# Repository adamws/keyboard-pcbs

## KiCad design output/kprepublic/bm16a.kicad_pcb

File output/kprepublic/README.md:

## kprepublic/bm16s

[layout](bm16s-kle.json) - [PCB](bm16s.kicad_pcb)

{:loading="lazy"}

[Open in keyboard-layout-editor](http://www.keyboard-layout-editor.com/##@@=0,0&=0,1&=0,2&=0,3;&@=1,0&=1,1&=1,2&=1,3;&@=2,0&=2,1&=2,2&=2,3;&@=3,0&=3,1&=3,2&=3,3)

{:loading="lazy"}

## kprepublic/bm40hsrgb

[layout](bm40hsrgb-kle.json) - [PCB](bm40hsrgb.kicad_pcb)

{:loading="lazy"}

[Open in keyboard-layout-editor](http://www.keyboard-layout-editor.com/##@@_c=#aaaaaa;&=0,0&_c=#ccccccc;&=0,1&=0,2&=0,3&=0,4&=0,5&=0,6&=0,7&=0,8&=0,9&=0,10&_c=#aaaaaa;&=0,11;&@_c=#777777;&=1,0&_c=#ccccccc;&=1,1&=1,2&=1,3&=1,4&=1,5&=1,6&=1,7&=1,8&=1,9&=1,10&_c=#aaaaaa;&=1,11;&@=2,0&_c=#ccccccc;&=2,1&=2,2&=2,3&=2,4&=2,5&=2,6&=2,7&=2,8&=2,9&=2,10&_c=#777777;&=2,11;&@_c=#aaaaaa;&=3,0&=3,1&=3,2&=3,3&=3,4&_w:2;&=3,5&=3,7&_c=#777777;&=3,8&=3,9&=3,10&=3,11)

{:loading="lazy"}

## kprepublic/bm60poker

[layout](bm60poker-kle.json) - [PCB](bm60poker.kicad_pcb)

{:loading="lazy"}

[Open in keyboard-layout-editor](http://www.keyboard-layout-editor.com/##@@_c=#777777;&=0,0&_c=#cccccc;&=0,1&=0,2&=0,3&=0,4&=0,5&=0,6&=0,7&=0,8&=0,9&=0,10&=0,11&=0,12&_c=#aaaaaa&w:2;&=0,13;&@_w:1.5;&=1,0&_c=#cccccc;&=1,1&=1,2&=1,3&=1,4&=1,5&=1,6&=1,7&=1,8&=1,9&=1,10&=1,11&=1,12&_w:1.5;&=1,13;&@_c=#aaaaaa&w:1.75;&=2,0&_c=#cccccc;&=2,2&=2,3&=2,4&=2,5&=2,6&=2,7&=2,8&=2,9&=2,10&=2,11&=2,12&_c=#777777&w:2.25;&=2,13;&@_c=#aaaaaa&w:2.25;&=3,1&_c=#cccccc;&=3,2&=3,3&=3,4&=3,5&=3,6&=3,7&=3,8&=3,9&=3,10&=3,11&_c=#aaaaaa&w:2.75;&=3,13;&@_w:1.25;&=4,0&_w:1.25;&=4,1&_w:1.25;&=4,2&_c=#cccccc&w:6.25;&=4,6&_c=#aaaaaa&w:1.25;&=4,9&_w:1.25;&=4,10&_w:1.25;&=4,12&_w:1.25;&=4,13)

{:loading="lazy"}

## kprepublic/bm60poker_v2

[layout](bm60poker_v2-kle.json) - [PCB](bm60poker_v2.kicad_pcb)

{:loading="lazy"}

[Open in keyboard-layout-editor](http://www.keyboard-layout-editor.com/##@@_c=#777777;&=0,0&_c=#cccccc;&=0,1&=0,2&=0,3&=0,4&=0,5&=0,6&=0,7&=0,8&=0,9&=0,10&=0,11&=0,12&_c=#aaaaaa&w:2;&=0,13;&@_w:1.5;&=1,0&_c=#cccccc;&=1,1&=1,2&=1,3&=1,4&=1,5&=1,6&=1,7&=1,8&=1,9&=1,10&=1,11&=1,12&_w:1.5;&=1,13;&@_c=#aaaaaa&w:1.75;&=2,0&_c=#cccccc;&=2,1&=2,2&=2,3&=2,4&=2,5&=2,6&=2,7&=2,8&=2,9&=2,10&=2,11&_c=#777777&w:2.25;&=2,13;&@_c=#aaaaaa&w:2.25;&=3,0&_c=#cccccc;&=3,1&=3,2&=3,3&=3,4&=3,5&=3,6&=3,7&=3,8&=3,9&=3,10&_c=#aaaaaa&w:2.75;&=3,13;&@_w:1.25;&=4,0&_w:1.25;&=4,1&_w:1.25;&=4,2&_c=#cccccc&w:6.25;&=4,5&_c=#aaaaaa&w:1.25;&=4,9&_w:1.25;&=4,10&_w:1.25;&=4,11&_w:1.25;&=4,13)

{:loading="lazy"}

## kprepublic/bm60rgb

[layout](bm60rgb-kle.json) - [PCB](bm60rgb.kicad_pcb)

{:loading="lazy"}

[Open in keyboard-layout-editor](http://www.keyboard-layout-editor.com/##@@_c=#777777;&=0,0&_c=#cccccc;&=0,1&=0,2&=0,3&=0,4&=0,5&=0,6&=0,7&=0,8&=0,9&=0,10&=0,11&=0,12&_c=#aaaaaa&w:2;&=0,13;&@_w:1.5;&=1,0&_c=#cccccc;&=1,1&=1,2&=1,3&=1,4&=1,5&=1,6&=1,7&=1,8&=1,9&=1,10&=1,11&=1,12&_w:1.5;&=1,13;&@_c=#aaaaaa&w:1.75;&=2,0&_c=#cccccc;&=2,2&=2,3&=2,4&=2,5&=2,6&=2,7&=2,8&=2,9&=2,10&=2,11&=2,12&_c=#777777&w:2.25;&=2,13;&@_c=#aaaaaa&w:2.25;&=3,1&_c=#cccccc;&=3,2&=3,3&=3,4&=3,5&=3,6&=3,7&=3,8&=3,9&=3,10&_c=#aaaaaa&w:1.75;&=3,11&_c=#777777;&=3,12&_c=#cccccc;&=3,13;&@_c=#aaaaaa&w:1.25;&=4,0&_w:1.25;&=4,1&_w:1.25;&=4,2&_c=#777777&w:6.25;&=4,6&_c=#aaaaaa;&=4,9&=4,10&_c=#777777;&=4,11&=4,12&=4,13)

{:loading="lazy"}

## kprepublic/bm60rgb_v2

[layout](bm60rgb_v2-kle.json) - [PCB](bm60rgb_v2.kicad_pcb)

{:loading="lazy"}

[Open in keyboard-layout-editor](http://www.keyboard-layout-editor.com/##@@_c=#777777;&=0,0&_c=#cccccc;&=0,1&=0,2&=0,3&=0,4&=0,5&=0,6&=0,7&=0,8&=0,9&=0,10&=0,11&=0,12&_c=#aaaaaa&w:2;&=0,13;&@_w:1.5;&=1,0&_c=#cccccc;&=1,1&=1,2&=1,3&=1,4&=1,5&=1,6&=1,7&=1,8&=1,9&=1,10&=1,11&=1,12&_w:1.5;&=1,13;&@_c=#aaaaaa&w:1.75;&=2,0&_c=#cccccc;&=2,2&=2,3&=2,4&=2,5&=2,6&=2,7&=2,8&=2,9&=2,10&=2,11&=2,12&_c=#777777&w:2.25;&=2,13;&@_c=#aaaaaa&w:2.25;&=3,1&_c=#cccccc;&=3,2&=3,3&=3,4&=3,5&=3,6&=3,7&=3,8&=3,9&=3,10&_c=#aaaaaa&w:1.75;&=3,11&_c=#777777;&=3,12&_c=#cccccc;&=3,13;&@_c=#aaaaaa&w:1.25;&=4,0&_w:1.25;&=4,1&_w:1.25;&=4,2&_c=#777777&w:6.25;&=4,6&_c=#aaaaaa;&=4,9&=4,10&_c=#777777;&=4,11&=4,12&=4,13)

{:loading="lazy"}

## kprepublic/bm60v2_ec

[layout](bm60v2_ec-kle.json) - [PCB](bm60v2_ec.kicad_pcb)

{:loading="lazy"}

[Open in keyboard-layout-editor](http://www.keyboard-layout-editor.com/##@@=0,0&=0,1&=0,2&=0,3&=0,4&=0,5&=0,6&=0,7&=0,8&=0,9&=0,10&=0,11&=0,12&=0,13&_x:0.75&w:0.75;&=4,3&=2,12&_w:0.75;&=4,4;&@_w:1.5;&=1,0&=1,1&=1,2&=1,3&=1,4&=1,5&=1,6&=1,7&=1,8&=1,9&=1,10&=1,11&=1,12&_w:1.5;&=1,13;&@_w:1.75;&=2,0&=2,1&=2,2&=2,3&=2,4&=2,5&=2,6&=2,7&=2,8&=2,9&=2,10&=2,11&_w:2.25;&=2,13;&@_w:2.25;&=3,0&=3,1&=3,2&=3,3&=3,4&=3,5&=3,6&=3,7&=3,8&=3,9&_w:1.75;&=3,11&=3,12&=3,13;&@_w:1.25;&=4,0&_w:1.25;&=4,1&_w:1.25;&=4,2&_w:6.25;&=4,6&=4,9&=4,10&=4,11&=4,12&=4,13)

{:loading="lazy"}

## kprepublic/bm68rgb

[layout](bm68rgb-kle.json) - [PCB](bm68rgb.kicad_pcb)

{:loading="lazy"}

[Open in keyboard-layout-editor](http://www.keyboard-layout-editor.com/##@@_c=#aaaaaa;&=0,0&_c=#cccccc;&=0,1&=0,2&=0,3&=0,4&=0,5&=0,6&=0,7&=0,8&=0,9&=0,10&=0,11&=0,12&_c=#777777&w:2;&=0,13&=0,14;&@_w:1.5;&=1,0&_c=#cccccc;&=1,1&=1,2&=1,3&=1,4&=1,5&=1,6&=1,7&=1,8&=1,9&=1,10&=1,11&=1,12&_w:1.5;&=1,13&_c=#777777;&=1,14;&@_w:1.75;&=2,0&_c=#cccccc;&=2,2&=2,3&=2,4&=2,5&=2,6&=2,7&=2,8&=2,9&=2,10&=2,11&=2,12&_c=#aaaaaa&w:2.25;&=2,13&_c=#777777;&=2,14;&@_w:2.25;&=3,1&_c=#cccccc;&=3,2&=3,3&=3,4&=3,5&=3,6&=3,7&=3,8&=3,9&=3,10&=3,11&_c=#777777&w:1.75;&=3,12&=3,13&=3,14;&@_w:1.25;&=4,0&_w:1.25;&=4,1&_w:1.25;&=4,2&_c=#aaaaaa&w:6.25;&=4,6&_c=#777777;&=4,9&=4,10&=4,11&=4,12&=4,13&=4,14)

{:loading="lazy"}

## kprepublic/bm80

[layout](bm80-kle.json) - [PCB](bm80.kicad_pcb)

{:loading="lazy"}

[Open in keyboard-layout-editor](http://www.keyboard-layout-editor.com/##@@_x:2.5&y:0.25&c=#777777;&=0,0&_x:1.0&c=#cccccc;&=0,2&=0,3&=0,4&=0,5&_x:0.5&c=#aaaaaa;&=0,7&=0,8&=0,9&=0,10&_x:0.5&c=#cccccc;&=0,11&=0,12&=3,12&=0,13&_x:0.25&c=#aaaaaa;&=0,14&=0,15&=0,16;&@_x:2.5&y:0.5&c=#cccccc;&=1,0&=1,1&=1,2&=1,3&=1,4&=1,5&=1,6&=1,7&=1,8&=1,9&=1,10&=1,11&=1,12&_c=#aaaaaa&w:2;&=1,13&_x:0.25;&=1,14&=1,15&=1,16;&@_x:2.5&w:1.5;&=2,0&_c=#cccccc;&=2,1&=2,2&=2,3&=2,4&=2,5&=2,6&=2,7&=2,8&=2,9&=2,10&=2,11&=2,12&_w:1.5;&=2,13&_x:0.25&c=#aaaaaa;&=2,14&=2,15&=2,16;&@_x:2.5&w:1.75;&=3,0&_c=#cccccc;&=3,1&=3,2&=3,3&=3,4&=3,5&=3,6&=3,7&=3,8&=3,9&=3,10&=3,11&_c=#777777&w:2.25;&=3,13;&@_x:2.5&c=#aaaaaa&w:2.25;&=4,0&=4,1&=4,2&=4,3&=4,4&=4,5&=4,6&=4,7&=4,8&=4,9&=4,10&_w:2.75;&=4,12&_x:1.25;&=4,15;&@_x:2.5&w:1.25;&=5,0&_w:1.25;&=5,1&_w:1.25;&=5,2&_c=#cccccc&w:6.25;&=5,5&_c=#aaaaaa&w:1.25;&=5,9&_w:1.25;&=5,10&_w:1.25;&=5,11&_w:1.25;&=5,12&_x:0.25;&=5,13&=5,15&=5,16)

{:loading="lazy"}

## kprepublic/bm980

[layout](bm980-kle.json) - [PCB](bm980.kicad_pcb)

{:loading="lazy"}

[Open in keyboard-layout-editor](http://www.keyboard-layout-editor.com/##@@_c=#777777;&=0,0&_x:1&c=#cccccc;&=0,1&=0,2&=0,3&=0,4&_x:0.5&c=#aaaaaa;&=0,5&=0,6&=0,7&=0,8&_x:0.5&c=#cccccc;&=0,9&=0,10&=0,11&=0,12&_x:1.0&c=#aaaaaa;&=0,13&=1,14&=1,10&=1,6;&@_y:0.5;&=2,0&_c=#cccccc;&=2,1&=2,2&=2,3&=2,4&=2,5&=2,6&=2,7&=2,8&=2,9&=2,10&=2,11&=2,12&_c=#aaaaaa&w:2;&=2,14&_x:1;&=2,13&=1,11&=1,9&=1,2;&@_w:1.5;&=3,0&_c=#cccccc;&=3,1&=3,2&=3,3&=3,4&=3,5&=3,6&=3,7&=3,8&=3,9&=3,10&=3,11&=3,12&_c=#aaaaaa&w:1.5;&=3,14&_x:1.0&c=#cccccc;&=3,13&=1,3&=1,4&_c=#aaaaaa&h:2;&=1,5;&@_w:1.75;&=4,0&_c=#cccccc;&=4,1&=4,2&=4,3&=4,4&=4,5&=4,6&=4,7&=4,8&=4,9&=4,10&=4,11&_c=#777777&w:2.25;&=4,14&_x:1.0&c=#cccccc;&=4,13&=1,8&=1,7;&@_c=#aaaaaa&w:2.25;&=5,0&_c=#cccccc;&=5,2&=5,3&=5,4&=5,5&=5,6&=5,7&=5,8&=5,9&=5,10&=5,11&_c=#aaaaaa&w:1.75;&=5,12&_x:2.0&c=#cccccc;&=5,13&=6,8&=6,7&_c=#aaaaaa&h:2;&=6,5;&@_x:14.5&y:-0.75&c=#777777;&=5,14;&@_y:-0.25&c=#aaaaaa&w:1.25;&=6,0&_w:1.25;&=6,1&_w:1.25;&=6,2&_c=#777777&w:6.25;&=6,6&_c=#aaaaaa;&=6,9&=6,10&=6,11&_x:4.0&c=#cccccc;&=6,3&=6,4;&@_x:13.5&y:-0.75&c=#777777;&=6,12&=6,14&=6,13)

{:loading="lazy"}

## kprepublic/cospad

[layout](cospad-kle.json) - [PCB](cospad.kicad_pcb)

{:loading="lazy"}

[Open in keyboard-layout-editor](http://www.keyboard-layout-editor.com/##@@_x:2.25&y:0.25;&=0,0&=0,1&=0,2&=0,3;&@_x:2.25;&=1,0&=1,1&=1,2&=1,3%0A%0A%0A0,0;&@_x:2.25;&=2,0&=2,1&=2,2&=2,3%0A%0A%0A0,0;&@_x:2.25;&=3,0&=3,1&=3,2&=3,3%0A%0A%0A0,0;&@_x:2.25;&=4,0%0A%0A%0A2,0&=4,1%0A%0A%0A2,0&=4,2&=4,3%0A%0A%0A0,0;&@_x:2.25;&=5,0%0A%0A%0A1,0&=5,1%0A%0A%0A1,0&=5,2&=5,3%0A%0A%0A0,0;&@_x:6.5&y:-5.0&h:2;&=1,3%0A%0A%0A0,1&=1,3%0A%0A%0A0,2&=1,3%0A%0A%0A0,3&=1,3%0A%0A%0A0,4&_h:2;&=1,3%0A%0A%0A0,5&_h:2;&=1,3%0A%0A%0A0,6&=1,3%0A%0A%0A0,7;&@_x:7.5&h:2;&=2,3%0A%0A%0A0,2&=2,3%0A%0A%0A0,3&=2,3%0A%0A%0A0,4&_x:2.0&h:2;&=2,3%0A%0A%0A0,7;&@_x:6.5;&=3,3%0A%0A%0A0,1&_x:1.0&h:2;&=3,3%0A%0A%0A0,3&=3,3%0A%0A%0A0,4&_h:2;&=3,3%0A%0A%0A0,5&=3,3%0A%0A%0A0,6;&@_w:2;&=4,0%0A%0A%0A2,1&_x:4.5;&=4,3%0A%0A%0A0,1&=4,3%0A%0A%0A0,2&_x:1.0&h:2;&=4,3%0A%0A%0A0,4&_x:1.0&h:2;&=4,3%0A%0A%0A0,6&_h:2;&=4,3%0A%0A%0A0,7;&@_x:6.5;&=5,3%0A%0A%0A0,1&=5,3%0A%0A%0A0,2&=5,3%0A%0A%0A0,3&_x:1.0;&=5,3%0A%0A%0A0,5;&@_x:2.25&y:0.25&w:2;&=5,0%0A%0A%0A1,1)

{:loading="lazy"}

## kprepublic/daisy40

[layout](daisy40-kle.json) - [PCB](daisy40.kicad_pcb)

{:loading="lazy"}

[Open in keyboard-layout-editor](http://www.keyboard-layout-editor.com/##@@_c=#777777;&=0,0&_c=#aaaaaa;&=0,1&=0,2&=0,3&=0,4&=0,5&=0,6&=0,7&=0,8&=0,9&=0,10&=3,10;&@_c=#cccccc&w:1.25;&=1,0&=1,1&=1,2&=1,3&=1,4&=1,5&=1,6&=1,7&=1,8&=1,9&_c=#777777&w:1.75;&=1,10;&@_c=#aaaaaa&w:1.75;&=2,0&=2,1&=2,2&=2,3&=2,4&=2,5&=2,6&=2,7&=2,8&=2,9&_w:1.25;&=2,10;&@_w:1.25;&=3,0&=3,1&=3,2%0A%0A%0A0,0&_c=#777777&w:6.25;&=3,5%0A%0A%0A0,0&_c=#aaaaaa&w:1.25;&=3,8%0A%0A%0A0,0&_w:1.25;&=3,9%0A%0A%0A0,0;&@_w:1.25;&=3,2%0A%0A%0A0,1&_c=#777777&w:2.5;&=3,4%0A%0A%0A0,1&_w:2.5;&=3,5%0A%0A%0A0,1&_c=#aaaaaa&w:1.25;&=3,7%0A%0A%0A0,1&=3,8%0A%0A%0A0,1&_w:1.25;&=3,9%0A%0A%0A0,1)

{:loading="lazy"}

## kprepublic/jj40

[layout](jj40-kle.json) - [PCB](jj40.kicad_pcb)

{:loading="lazy"}

[Open in keyboard-layout-editor](http://www.keyboard-layout-editor.com/##@@_c=#aaaaaa;&=0,0&_c=#ccccccc;&=0,1&=0,2&=0,3&=0,4&=0,5&=0,6&=0,7&=0,8&=0,9&=0,10&_c=#aaaaaa;&=0,11;&@_c=#777777;&=1,0&_c=#ccccccc;&=1,1&=1,2&=1,3&=1,4&=1,5&=1,6&=1,7&=1,8&=1,9&=1,10&_c=#aaaaaa;&=1,11;&@=2,0&_c=#ccccccc;&=2,1&=2,2&=2,3&=2,4&=2,5&=2,6&=2,7&=2,8&=2,9&=2,10&_c=#777777;&=2,11;&@_c=#aaaaaa;&=3,0&=3,1&=3,2&=3,3&=3,4%0A%0A%0A0,0&=3,5%0A%0A%0A0,0&=3,6%0A%0A%0A0,0&=3,7%0A%0A%0A0,0&_c=#777777;&=3,8&=3,9&=3,10&=3,11;&@_x:4&c=#aaaaaa;&=3,4%0A%0A%0A0,1&_w:2;&=3,5%0A%0A%0A0,1&=3,7%0A%0A%0A0,1;&@_x:4&w:2;&=3,4%0A%0A%0A0,2&=3,6%0A%0A%0A0,2&=3,7%0A%0A%0A0,2;&@_x:4;&=3,4%0A%0A%0A0,3&=3,5%0A%0A%0A0,3&_w:2;&=3,6%0A%0A%0A0,3;&@_x:4&w:2;&=3,4%0A%0A%0A0,4&_w:2;&=3,6%0A%0A%0A0,4)

{:loading="lazy"}

## kprepublic/jj4x4

[layout](jj4x4-kle.json) - [PCB](jj4x4.kicad_pcb)

{:loading="lazy"}

[Open in keyboard-layout-editor](http://www.keyboard-layout-editor.com/##@@=0,0&=0,1&=0,2&=0,3;&@=1,0&=1,1&=1,2&=1,3;&@=2,0&=2,1&=2,2&=2,3;&@=3,0&=3,1&=3,2&=3,3)

{:loading="lazy"}

## kprepublic/jj50

[layout](jj50-kle.json) - [PCB](jj50.kicad_pcb)

{:loading="lazy"}

[Open in keyboard-layout-editor](http://www.keyboard-layout-editor.com/##@@_c=#777777;&=0,0&_c=#ccccccc;&=0,1&=0,2&=0,3&=0,4&=0,5&=0,6&=0,7&=0,8&=0,9&=0,10&_c=#aaaaaa;&=0,11;&@=1,0&_c=#ccccccc;&=1,1&=1,2&=1,3&=1,4&=1,5&=1,6&=1,7&=1,8&=1,9&=1,10&_c=#aaaaaa;&=1,11;&@_c=#777777;&=2,0&_c=#ccccccc;&=2,1&=2,2&=2,3&=2,4&=2,5&=2,6&=2,7&=2,8&=2,9&=2,10&_c=#aaaaaa;&=2,11;&@=3,0&_c=#ccccccc;&=3,1&=3,2&=3,3&=3,4&=3,5&=3,6&=3,7&=3,8&=3,9&=3,10&_c=#777777;&=3,11;&@_c=#aaaaaa;&=4,0&=4,1&=4,2&=4,3&=4,4%0A%0A%0A0,0&=4,5%0A%0A%0A0,0&=4,6%0A%0A%0A0,0&=4,7%0A%0A%0A0,0&_c=#777777;&=4,8&=4,9&=4,10&=4,11;&@_x:4&c=#aaaaaa;&=4,4%0A%0A%0A0,1&_w:2;&=4,5%0A%0A%0A0,1&=4,7%0A%0A%0A0,1;&@_x:4&w:2;&=4,4%0A%0A%0A0,2&=4,6%0A%0A%0A0,2&=4,7%0A%0A%0A0,2;&@_x:4;&=4,4%0A%0A%0A0,3&=4,5%0A%0A%0A0,3&_w:2;&=4,6%0A%0A%0A0,3;&@_x:4&w:2;&=4,4%0A%0A%0A0,4&_w:2;&=4,6%0A%0A%0A0,4)

{:loading="lazy"}

## kprepublic/xd75

[layout](xd75-kle.json) - [PCB](xd75.kicad_pcb)

{:loading="lazy"}

[Open in keyboard-layout-editor](http://www.keyboard-layout-editor.com/##@@_c=#777777;&=0,0&_c=#cccccc;&=0,1&=0,2&=0,3&=0,4&=0,5&=0,6&=0,7&=0,8&=0,9&=0,10&=0,11&=0,12&=0,13&_c=#aaaaaa;&=0,14;&@=1,0&_c=#cccccc;&=1,1&=1,2&=1,3&=1,4&=1,5&=1,6&=1,7&=1,8&=1,9&=1,10&=1,11&=1,12&=1,13&=1,14;&@_c=#aaaaaa;&=2,0&_c=#cccccc;&=2,1&=2,2&=2,3&=2,4&=2,5&_c=#aaaaaa;&=2,6&=2,7&=2,8&_c=#cccccc;&=2,9&=2,10&=2,11&=2,12&=2,13&_c=#777777;&=2,14;&@_c=#aaaaaa;&=3,0&_c=#cccccc;&=3,1&=3,2&=3,3&=3,4&=3,5&_c=#aaaaaa;&=3,6&_c=#777777;&=3,7&_c=#aaaaaa;&=3,8&_c=#cccccc;&=3,9&=3,10&=3,11&=3,12&=3,13&_c=#aaaaaa;&=3,14;&@=4,0&=4,1&=4,2&=4,3&_c=#cccccc;&=4,4&=4,5&_c=#777777;&=4,6&=4,7&=4,8&_c=#cccccc;&=4,9&=4,10&_c=#aaaaaa;&=4,11&=4,12&=4,13&=4,14)

{:loading="lazy"}

## kprepublic/xd84pro

[layout](xd84pro-kle.json) - [PCB](xd84pro.kicad_pcb)

{:loading="lazy"}

[Open in keyboard-layout-editor](http://www.keyboard-layout-editor.com/##@@_x:3&c=#777777;&=0,0&_c=#cccccc;&=0,1&=0,2&=0,3&=0,4&_c=#aaaaaa;&=0,5&=0,6&=0,7&=0,8&_c=#cccccc;&=0,9&=0,10&=0,11&=0,12&_c=#aaaaaa;&=0,13%0A%0A%0A0,0&=5,6%0A%0A%0A0,0&=0,14%0A%0A%0A0,0;&@_x:3&c=#cccccc;&=1,0&=1,1&=1,2&=1,3&=1,4&=1,5&=1,6&=1,7&=1,8&=1,9&=1,10&=1,11&=1,12&_c=#aaaaaa&w:2;&=1,13%0A%0A%0A1,0&=1,14%0A%0A%0A1,0;&@_x:3&w:1.5;&=2,0&_c=#cccccc;&=2,1&=2,2&=2,3&=2,4&=2,5&=2,6&=2,7&=2,8&=2,9&=2,10&=2,11&=2,12&_w:1.5;&=2,13%0A%0A%0A2,0&_c=#aaaaaa;&=2,14;&@_x:3&w:1.75;&=3,0&_c=#cccccc;&=3,1&=3,2&=3,3&=3,4&=3,5&=3,6&=3,7&=3,8&=3,9&=3,10&=3,11&_c=#777777&w:2.25;&=3,13%0A%0A%0A2,0&_c=#aaaaaa;&=3,14;&@_x:3.0&w:2.25;&=4,0%0A%0A%0A3,0&_c=#cccccc;&=4,2&=4,3&=4,4&=4,5&=4,6&=4,7&=4,8&=4,9&=4,10&=4,11&_c=#aaaaaa&w:1.75;&=4,12%0A%0A%0A4,0&=4,13%0A%0A%0A4,0&=4,14%0A%0A%0A4,0;&@_x:3&w:1.25;&=5,0%0A%0A%0A5,0&_w:1.25;&=5,1%0A%0A%0A5,0&_w:1.25;&=5,2%0A%0A%0A5,0&_c=#777777&w:6.25;&=5,5%0A%0A%0A5,0&_c=#aaaaaa;&=5,10%0A%0A%0A5,0&=5,11%0A%0A%0A5,0&=5,8%0A%0A%0A5,0&=5,12%0A%0A%0A5,0&=5,13%0A%0A%0A5,0&=5,14%0A%0A%0A5,0;&@_x:19.75&y:-6&c=#cccccc;&=0,13%0A%0A%0A0,1&_c=#aaaaaa&w:2;&=5,6%0A%0A%0A0,1;&@_x:19.75&c=#cccccc;&=1,13%0A%0A%0A1,1&=5,9%0A%0A%0A1,1&=1,14%0A%0A%0A1,1&_x:0.75;&=1,13%0A%0A%0A1,2&_c=#aaaaaa&w:2;&=5,9%0A%0A%0A1,2;&@_x:20.5&c=#777777&w:1.25&h:2&w2:1.5&h2:1&x2:-0.25;&=3,13%0A%0A%0A2,1;&@_x:19.5&c=#cccccc;&=3,12%0A%0A%0A2,1;&@_c=#aaaaaa&w:1.25;&=4,0%0A%0A%0A3,1&_c=#cccccc;&=4,1%0A%0A%0A3,1&_x:17.25&c=#aaaaaa&w:1.25;&=4,12%0A%0A%0A4,1&_w:1.25;&=4,13%0A%0A%0A4,1&_w:1.25;&=4,14%0A%0A%0A4,1;&@_x:3&y:1.25&w:1.25;&=5,0%0A%0A%0A5,1&_w:1.25;&=5,1%0A%0A%0A5,1&_w:1.25;&=5,2%0A%0A%0A5,1&_c=#777777&w:6.25;&=5,5%0A%0A%0A5,1&_c=#aaaaaa;&=5,10%0A%0A%0A5,1&_w:1.25;&=5,11%0A%0A%0A5,1&_w:1.25;&=5,12%0A%0A%0A5,1&_w:1.25;&=5,13%0A%0A%0A5,1&_w:1.25;&=5,14%0A%0A%0A5,1;&@_x:3&y:0.25&w:1.25;&=5,0%0A%0A%0A5,2&_w:1.25;&=5,1%0A%0A%0A5,2&_w:1.25;&=5,2%0A%0A%0A5,2&_c=#777777&w:6.25;&=5,5%0A%0A%0A5,2&_c=#aaaaaa&w:1.25;&=5,10%0A%0A%0A5,2&=5,11%0A%0A%0A5,2&_w:1.25;&=5,12%0A%0A%0A5,2&_w:1.25;&=5,13%0A%0A%0A5,2&_w:1.25;&=5,14%0A%0A%0A5,2;&@_x:3&y:0.25&w:1.5;&=5,0%0A%0A%0A5,3&_w:1.5;&=5,1%0A%0A%0A5,3&_c=#777777&w:7;&=5,5%0A%0A%0A5,3&_c=#aaaaaa&w:1.5;&=5,10%0A%0A%0A5,3&_w:1.5;&=5,11%0A%0A%0A5,3&=5,12%0A%0A%0A5,3&=5,13%0A%0A%0A5,3&=5,14%0A%0A%0A5,3;&@_x:3&y:0.25&w:1.5;&=5,0%0A%0A%0A5,4&=5,1%0A%0A%0A5,4&_w:1.5;&=5,2%0A%0A%0A5,4&_c=#777777&w:6;&=5,5%0A%0A%0A5,4&_c=#aaaaaa;&=5,10%0A%0A%0A5,4&=5,11%0A%0A%0A5,4&=5,8%0A%0A%0A5,4&=5,12%0A%0A%0A5,4&=5,13%0A%0A%0A5,4&=5,14%0A%0A%0A5,4;&@_x:3&y:0.25&w:1.5;&=5,0%0A%0A%0A5,5&=5,1%0A%0A%0A5,5&_w:1.25;&=5,2%0A%0A%0A5,5&_c=#777777&w:6.25;&=5,5%0A%0A%0A5,5&_c=#aaaaaa;&=5,10%0A%0A%0A5,5&=5,11%0A%0A%0A5,5&=5,8%0A%0A%0A5,5&=5,12%0A%0A%0A5,5&=5,13%0A%0A%0A5,5&=5,14%0A%0A%0A5,5;&@_x:3&y:0.25&w:1.5;&=5,0%0A%0A%0A5,6&=5,1%0A%0A%0A5,6&_w:1.5;&=5,2%0A%0A%0A5,6&_c=#777777&w:7;&=5,5%0A%0A%0A5,6&_c=#aaaaaa;&=5,11%0A%0A%0A5,6&=5,8%0A%0A%0A5,6&=5,12%0A%0A%0A5,6&=5,13%0A%0A%0A5,6&=5,14%0A%0A%0A5,6;&@_x:3&y:0.25&w:1.25;&=5,0%0A%0A%0A5,7&_w:1.25;&=5,1%0A%0A%0A5,7&_w:1.25;&=5,2%0A%0A%0A5,7&_c=#777777&w:6.25;&=5,5%0A%0A%0A5,7&_c=#aaaaaa&w:1.5;&=5,10%0A%0A%0A5,7&_w:1.5;&=5,11%0A%0A%0A5,7&=5,12%0A%0A%0A5,7&=5,13%0A%0A%0A5,7&=5,14%0A%0A%0A5,7)

{:loading="lazy"}

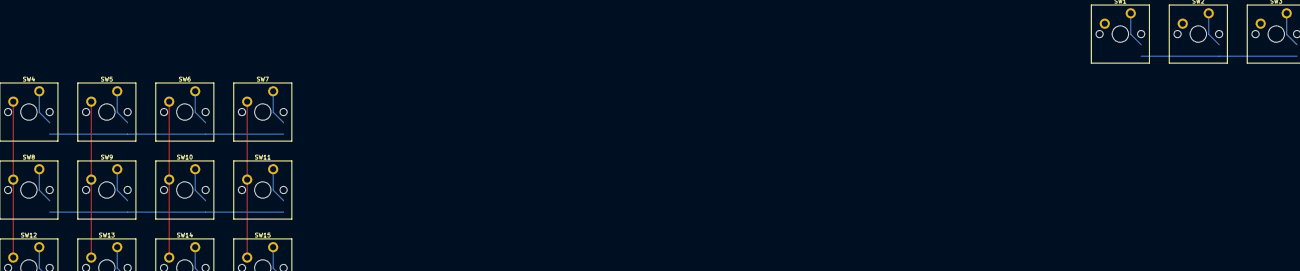
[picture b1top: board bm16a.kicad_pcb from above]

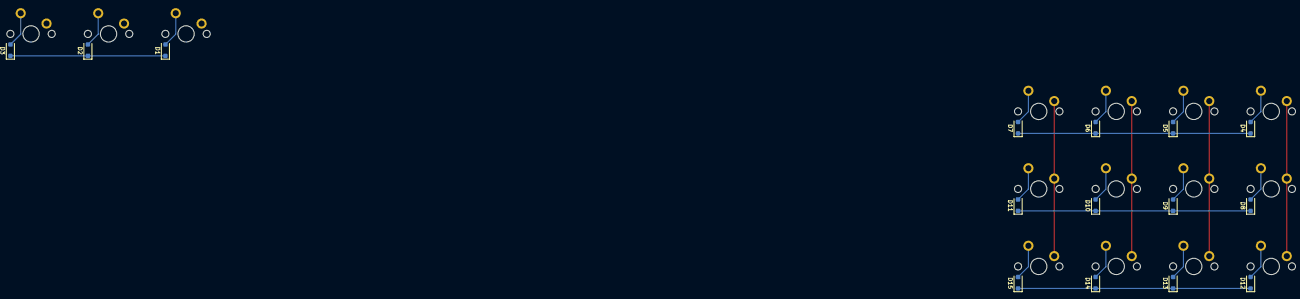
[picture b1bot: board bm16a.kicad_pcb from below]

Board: 2 copper layers, 30 parts (15 on the bottom side), 23 nets.

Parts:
D1, D2, D3, D4, D5, D6, D7, D8, D9, D10, D11, D12, D13, D14, D15: D_SOD-123F
SW1, SW2, SW3, SW4, SW5, SW6, SW7, SW8, SW9, SW10, SW11, SW12, SW13, SW14, SW15: SW_Cherry_MX_PCB_1.00u

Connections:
COL0: SW4.1, SW8.1, SW12.1
COL1: SW1.1, SW5.1, SW9.1, SW13.1
COL2: SW2.1, SW6.1, SW10.1, SW14.1
COL3: SW3.1, SW7.1, SW11.1, SW15.1
unnamed: D1.2, SW1.2
unnamed: D2.2, SW2.2
unnamed: D3.2, SW3.2
unnamed: D4.2, SW4.2
unnamed: D5.2, SW5.2
unnamed: D6.2, SW6.2
unnamed: D7.2, SW7.2
unnamed: D8.2, SW8.2
unnamed: D9.2, SW9.2
unnamed: D10.2, SW10.2
unnamed: D11.2, SW11.2
unnamed: D12.2, SW12.2
unnamed: D13.2, SW13.2
unnamed: D14.2, SW14.2
unnamed: D15.2, SW15.2
ROW0: D1.1, D2.1, D3.1
ROW1: D4.1, D5.1, D6.1, D7.1
ROW2: D8.1, D9.1, D10.1, D11.1
ROW3: D12.1, D13.1, D14.1, D15.1

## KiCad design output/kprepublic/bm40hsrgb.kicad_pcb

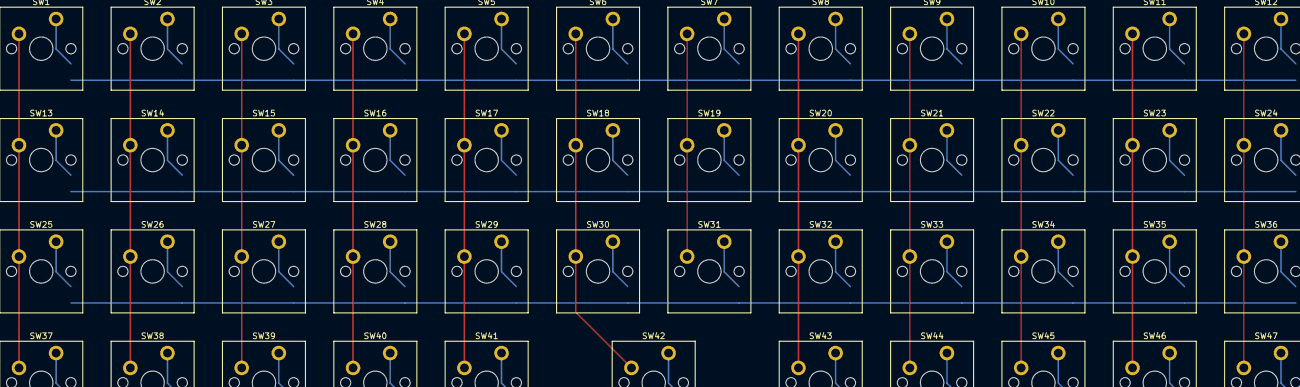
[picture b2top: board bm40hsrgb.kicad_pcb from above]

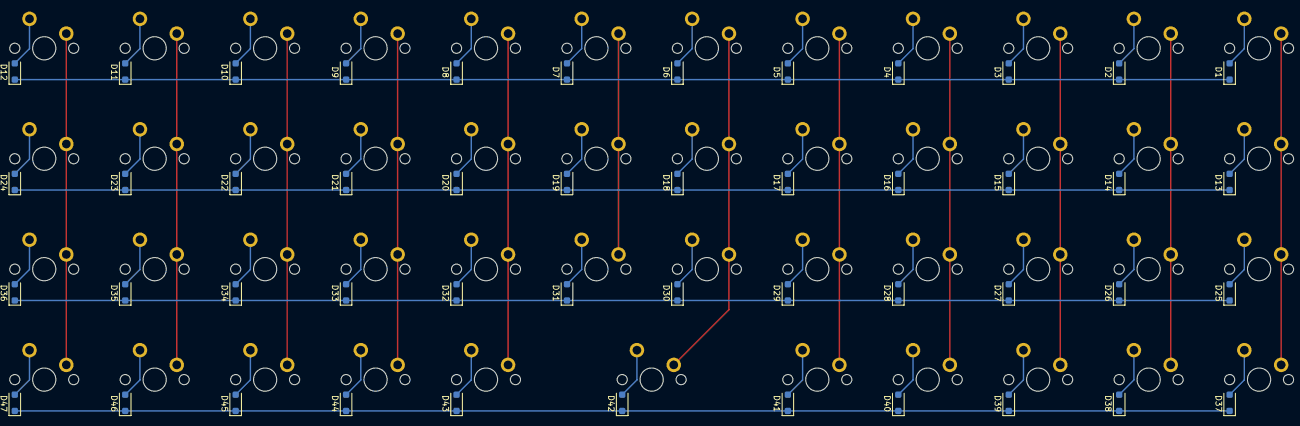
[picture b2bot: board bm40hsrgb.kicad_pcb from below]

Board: 2 copper layers, 94 parts (47 on the bottom side), 63 nets.

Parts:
D1, D2, D3, D4, D5, D6, D7, D8, D9, D10, D11, D12, D13, D14, D15, D16, D17, D18, D19, D20, D21, D22, D23, D24, D25, D26, D27, D28, D29, D30, D31, D32, D33, D34, D35, D36, D37, D38, D39, D40, D41, D42, D43, D44, D45, D46, D47: D_SOD-123F
SW1, SW2, SW3, SW4, SW5, SW6, SW7, SW8, SW9, SW10, SW11, SW12, SW13, SW14, SW15, SW16, SW17, SW18, SW19, SW20, SW21, SW22, SW23, SW24, SW25, SW26, SW27, SW28, SW29, SW30, SW31, SW32, SW33, SW34, SW35, SW36, SW37, SW38, SW39, SW40, SW41, SW42, SW43, SW44, SW45, SW46, SW47: SW_Cherry_MX_PCB_1.00u

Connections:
COL0: SW1.1, SW13.1, SW25.1, SW37.1
COL1: SW2.1, SW14.1, SW26.1, SW38.1
COL2: SW3.1, SW15.1, SW27.1, SW39.1
COL3: SW4.1, SW16.1, SW28.1, SW40.1
COL4: SW5.1, SW17.1, SW29.1, SW41.1
COL5: SW6.1, SW18.1, SW30.1, SW42.1
COL6: SW7.1, SW19.1, SW31.1
COL7: SW8.1, SW20.1, SW32.1, SW43.1
COL8: SW9.1, SW21.1, SW33.1, SW44.1
COL9: SW10.1, SW22.1, SW34.1, SW45.1
COL10: SW11.1, SW23.1, SW35.1, SW46.1
COL11: SW12.1, SW24.1, SW36.1, SW47.1
unnamed: D1.2, SW1.2
unnamed: D2.2, SW2.2
unnamed: D3.2, SW3.2
unnamed: D4.2, SW4.2
unnamed: D5.2, SW5.2
unnamed: D6.2, SW6.2
unnamed: D7.2, SW7.2
unnamed: D8.2, SW8.2
unnamed: D9.2, SW9.2
unnamed: D10.2, SW10.2
unnamed: D11.2, SW11.2
unnamed: D12.2, SW12.2
unnamed: D13.2, SW13.2
unnamed: D14.2, SW14.2
unnamed: D15.2, SW15.2
unnamed: D16.2, SW16.2
unnamed: D17.2, SW17.2
unnamed: D18.2, SW18.2
unnamed: D19.2, SW19.2
unnamed: D20.2, SW20.2
unnamed: D21.2, SW21.2
unnamed: D22.2, SW22.2
unnamed: D23.2, SW23.2
unnamed: D24.2, SW24.2
unnamed: D25.2, SW25.2
unnamed: D26.2, SW26.2
unnamed: D27.2, SW27.2
unnamed: D28.2, SW28.2
unnamed: D29.2, SW29.2
unnamed: D30.2, SW30.2
unnamed: D31.2, SW31.2
unnamed: D32.2, SW32.2
unnamed: D33.2, SW33.2
unnamed: D34.2, SW34.2
unnamed: D35.2, SW35.2
unnamed: D36.2, SW36.2
unnamed: D37.2, SW37.2
unnamed: D38.2, SW38.2
unnamed: D39.2, SW39.2
unnamed: D40.2, SW40.2
unnamed: D41.2, SW41.2
unnamed: D42.2, SW42.2
unnamed: D43.2, SW43.2
unnamed: D44.2, SW44.2
unnamed: D45.2, SW45.2
unnamed: D46.2, SW46.2
unnamed: D47.2, SW47.2
ROW0: D1.1, D2.1, D3.1, D4.1, D5.1, D6.1, D7.1, D8.1, D9.1, D10.1, D11.1, D12.1
ROW1: D13.1, D14.1, D15.1, D16.1, D17.1, D18.1, D19.1, D20.1, D21.1, D22.1, D23.1, D24.1
ROW2: D25.1, D26.1, D27.1, D28.1, D29.1, D30.1, D31.1, D32.1, D33.1, D34.1, D35.1, D36.1
ROW3: D37.1, D38.1, D39.1, D40.1, D41.1, D42.1, D43.1, D44.1, D45.1, D46.1, D47.1
